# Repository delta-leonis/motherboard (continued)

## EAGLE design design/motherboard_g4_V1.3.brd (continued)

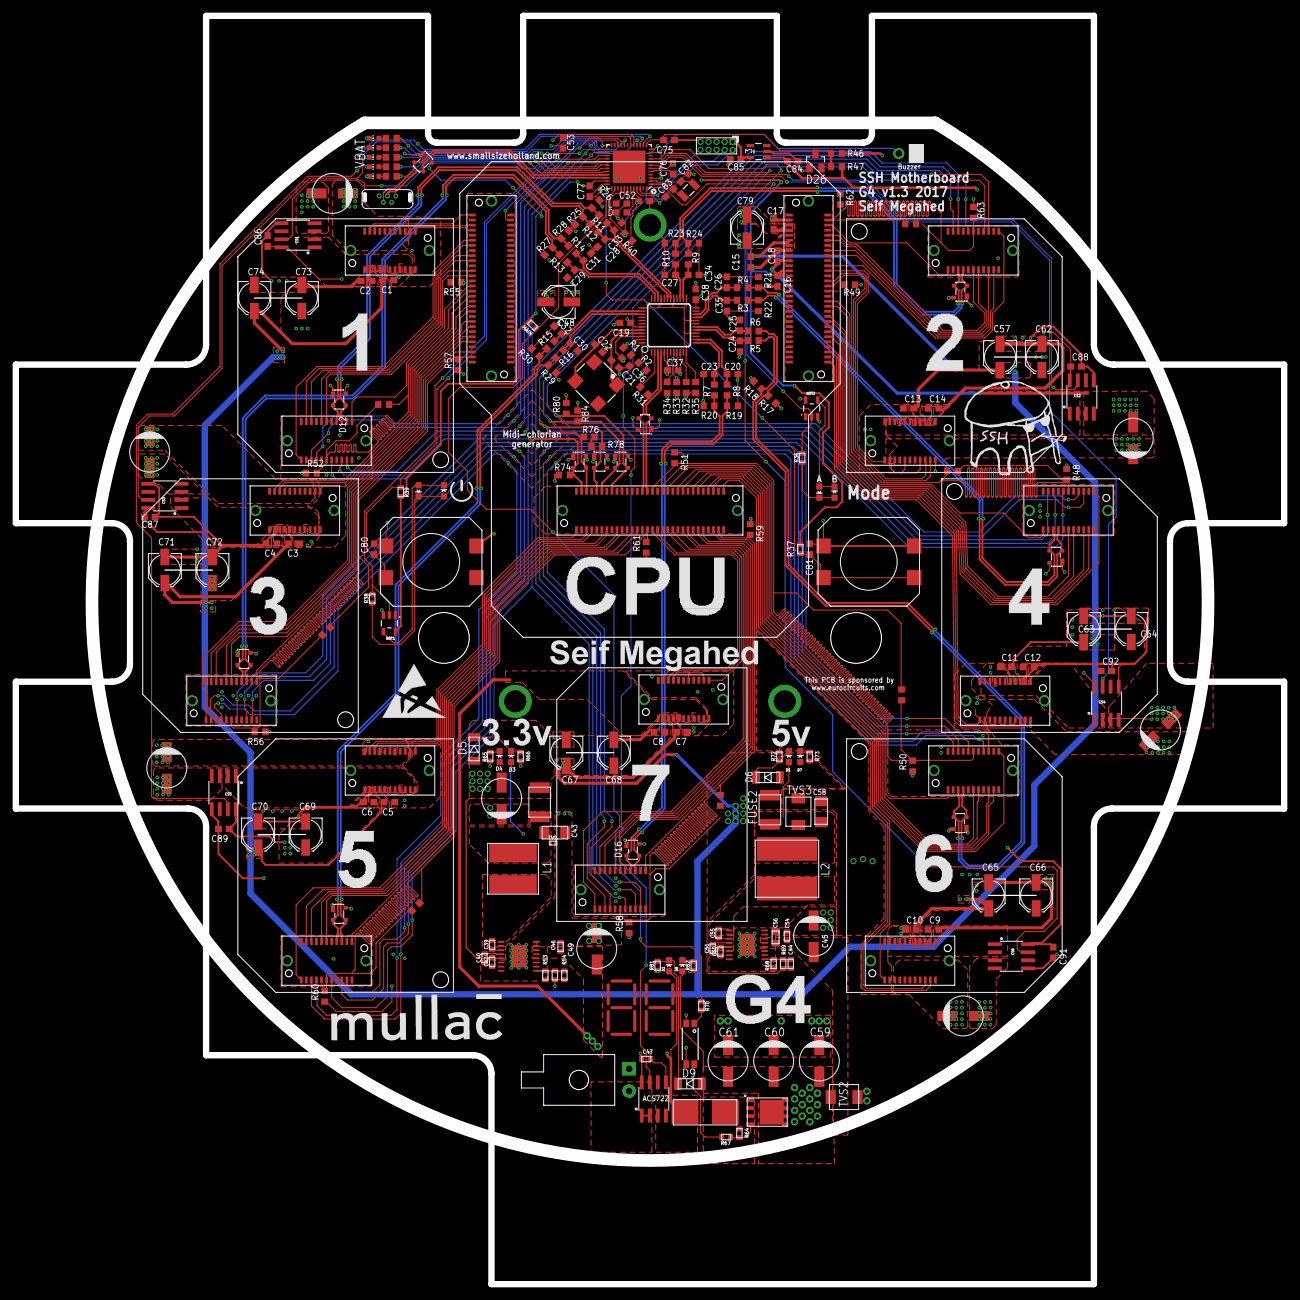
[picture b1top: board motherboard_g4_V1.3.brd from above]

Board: 4 copper layers, 200.0 x 200.0 mm, 260 parts (0 on the bottom side), 187 nets.

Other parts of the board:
U$10: ESD_10.00
U$15: SSH_LOGO
U$18: LOGO

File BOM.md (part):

| Part  | Value                                                                                                              | Device                                | Package              | Farnell ID                           | Mouser ID | Man          |
|-------|--------------------------------------------------------------------------------------------------------------------|---------------------------------------|----------------------|--------------------------------------|-----------|--------------|
| CS0   | ACS712                                                                                                             | ACS711                                | SO08                 |                                      |           |              |
| CS1   | ACS712                                                                                                             | ACS711                                | SO08                 |                                      |           |              |
| CS2   | ACS712                                                                                                             | ACS711                                | SO08                 |                                      |           |              |
| CS3   | ACS712                                                                                                             | ACS711                                | SO08                 |                                      |           |              |
| CS4   | ACS712                                                                                                             | ACS711                                | SO08                 |                                      |           |              |
| CS5   | ACS712                                                                                                             | ACS711                                | SO08                 |                                      |           |              |
| CS6   | ACS712                                                                                                             | ACS711                                | SO08                 |                                      |           |              |
| U2    | ATSAMLQFN-48-NO-VIA                                                                                                | ATSAMD                                | QFN-48               |                                      |           |              |
| C84   | 1u                                                                                                                 | Ceramic_Capacitor                     | _0603                |                                      |           |              |
| C85   | 2.2u                                                                                                               | Ceramic_Capacitor                     | _0603                |                                      |           |              |
| C56   | 6.8u                                                                                                               | Ceramic_Capacitor                     | _0805                |                                      |           |              |
| C42   | 1u                                                                                                                 | Ceramic_Capacitor                     | _0603                |                                      |           |              |
| C50   | 1u                                                                                                                 | Ceramic_Capacitor                     | _0603                |                                      |           |              |
| C40   | 2.2u                                                                                                               | Ceramic_Capacitor                     | _0603                |                                      |           |              |
| C51   | 2.2u                                                                                                               | Ceramic_Capacitor                     | _0603                |                                      |           |              |
| C1    | 100n                                                                                                               | Ceramic_Capacitor                     | _0603                |                                      |           |              |
| C2    | 100n                                                                                                               | Ceramic_Capacitor                     | _0603                |                                      |           |              |
| C3    | 100n                                                                                                               | Ceramic_Capacitor                     | _0603                |                                      |           |              |
| C4    | 100n                                                                                                               | Ceramic_Capacitor                     | _0603                |                                      |           |              |
| C5    | 100n                                                                                                               | Ceramic_Capacitor                     | _0603                |                                      |           |              |
| C6    | 100n                                                                                                               | Ceramic_Capacitor                     | _0603                |                                      |           |              |
| C7    | 100n                                                                                                               | Ceramic_Capacitor                     | _0603                |                                      |           |              |
| C8    | 100n                                                                                                               | Ceramic_Capacitor                     | _0603                |                                      |           |              |
| C9    | 100n                                                                                                               | Ceramic_Capacitor                     | _0603                |                                      |           |              |
| C10   | 100n                                                                                                               | Ceramic_Capacitor                     | _0603                |                                      |           |              |
| C11   | 100n                                                                                                               | Ceramic_Capacitor                     | _0603                |                                      |           |              |
| C12   | 100n                                                                                                               | Ceramic_Capacitor                     | _0603                |                                      |           |              |
| C13   | 100n                                                                                                               | Ceramic_Capacitor                     | _0603                |                                      |           |              |
| C14   | 100n                                                                                                               | Ceramic_Capacitor                     | _0603                |                                      |           |              |
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
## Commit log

2017-11-06 here be dragons
2017-11-06 added files to initial commit
2017-11-07 added gitignore, fixed math in readme
2017-11-07 removed .files
2017-11-07 removed versioning fixed other stuff as well
2017-11-07 added header to README
2017-11-07 README update
2017-11-07 fixed header and /credit.md
2017-11-07 initial commit (#1)
    * added files to initial commit
    * added gitignore, fixed math in readme
    * removed .files
    * removed versioning fixed other stuff as well
    * added header to README
    * README update
2017-11-15 fix readme
2017-11-16 fix readme (#2)
